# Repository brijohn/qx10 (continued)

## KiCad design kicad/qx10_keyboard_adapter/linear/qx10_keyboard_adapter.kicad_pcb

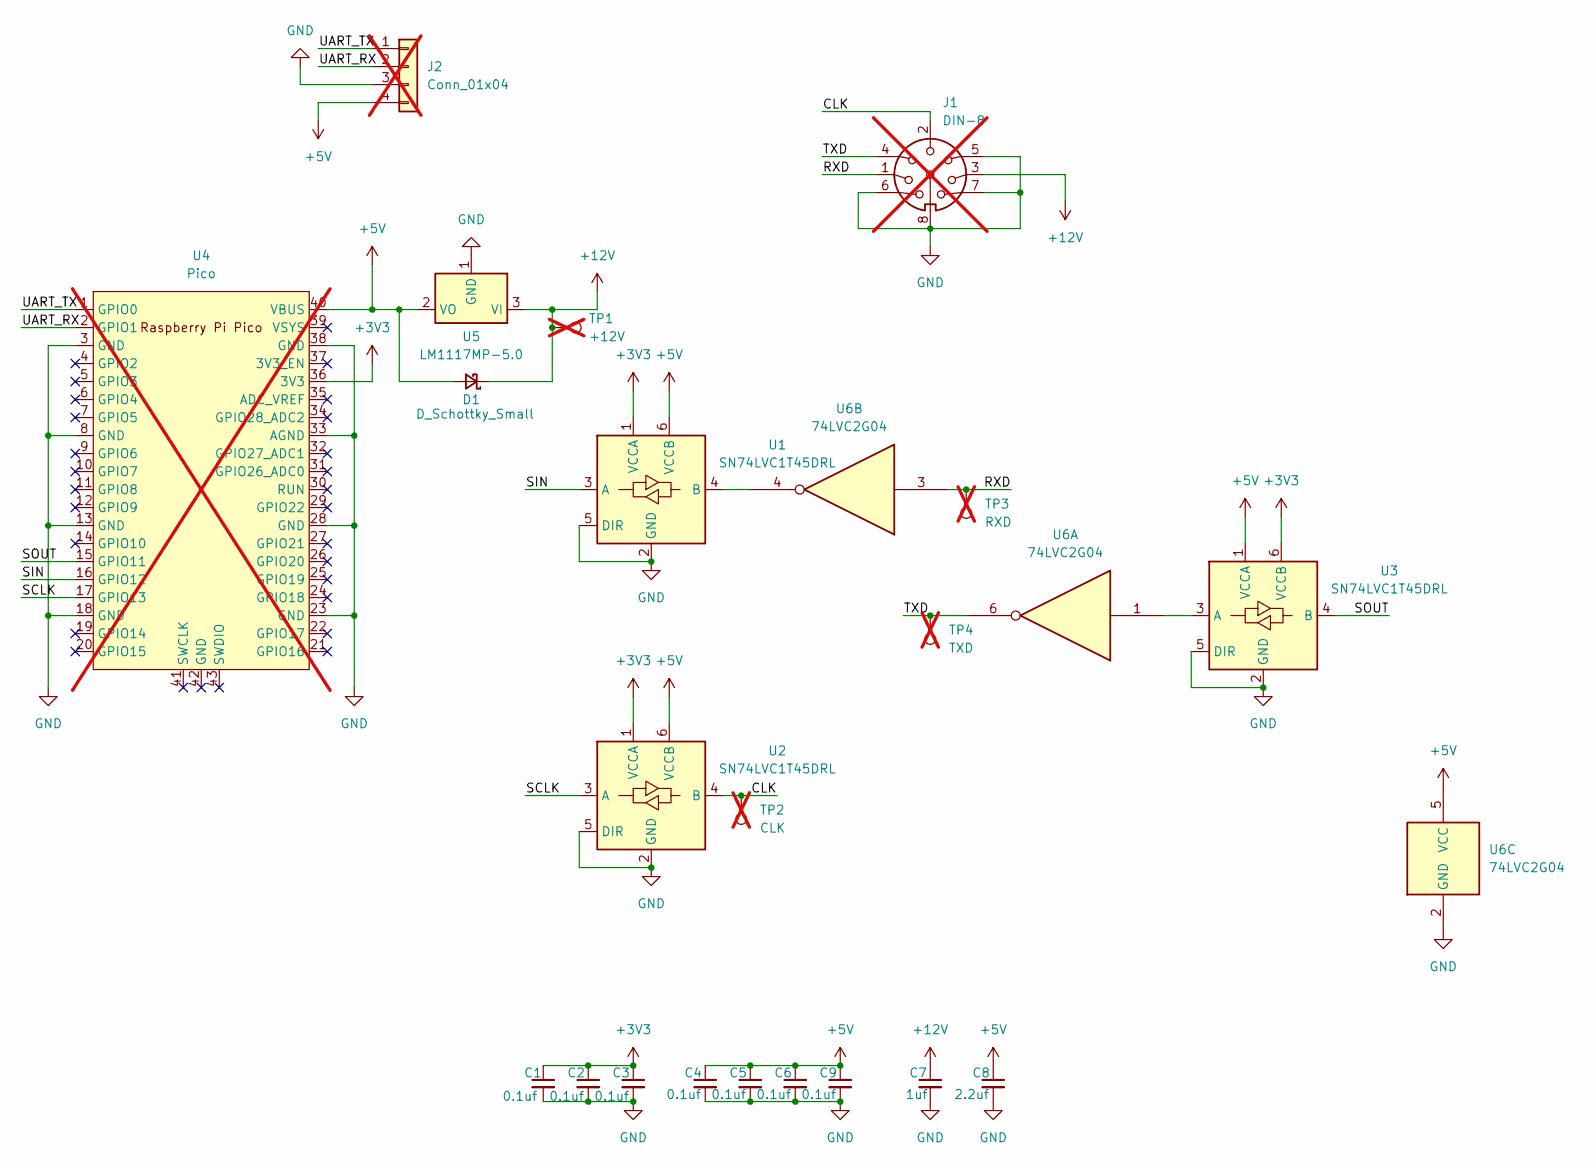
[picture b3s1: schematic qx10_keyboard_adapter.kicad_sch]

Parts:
C1, C2, C3, C4, C5, C6, C9: 0.1uf; C_0603_1608Metric_Pad1.08x0.95mm_HandSolder; JLC 0603
C7: 1uf; C_0603_1608Metric_Pad1.08x0.95mm_HandSolder; JLC 0603
C8: 2.2uf; C_0603_1608Metric_Pad1.08x0.95mm_HandSolder; JLC 0603
D1: D_Schottky_Small; D_SMA_Handsoldering; JLC SMA(DO-214AC)
J1: DIN-8; 8DIN262; not fitted
J2: Conn_01x04; PinHeader_1x04_P2.54mm_Vertical; not fitted
TP1: +12V; TestPoint_Pad_2.5x2.5mm; not fitted
TP2: CLK; TestPoint_Pad_2.5x2.5mm; not fitted
TP3: RXD; TestPoint_Pad_2.5x2.5mm; not fitted
TP4: TXD; TestPoint_Pad_2.5x2.5mm; not fitted
U1, U2, U3: SN74LVC1T45DRL; SOT-563; JLC SOT-5x3-6
U4: Pico; RPi_Pico_SMD_TH; not fitted
U5: LM1117MP-5.0; SOT-223-3_TabPin2; JLC SOT-223
U6: 74LVC2G04; SOT-23-6; JLC SOT-23-6

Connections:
+3V3: C1.1, C2.1, C3.1, U1.1 (VCCA), U2.1 (VCCA), U3.6 (VCCB), U4.36 (3V3)
+5V: C4.1, C5.1, C6.1, C8.1, C9.1, D1.2 (A), J2.4, U1.6 (VCCB), U2.6 (VCCB), U3.1 (VCCA), U4.40 (VBUS), U5.2 (VO), U6.5 (VCC)
+12V: C7.1, D1.1 (K), J1.3, TP1.1, U5.3 (VI)
/CLK: J1.2, TP2.1, U2.4 (B)
/RXD: J1.1, TP3.1, U6.3
/SCLK: U2.3 (A), U4.17 (GPIO13)
/SIN: U1.3 (A), U4.16 (GPIO12)
/SOUT: U3.4 (B), U4.15 (GPIO11)
/TXD: J1.4, TP4.1, U6.6
/UART_RX: J2.2, U4.2 (GPIO1)
/UART_TX: J2.1, U4.1 (GPIO0)
GND: C1.2, C2.2, C3.2, C4.2, C5.2, C6.2, C7.2, C8.2, C9.2, J1.5, J1.6, J1.7, J1.8, J2.3, U1.2 (GND), U1.5 (DIR), U2.2 (GND), U2.5 (DIR), U3.2 (GND), U3.5 (DIR), U4.3 (GND), U4.8 (GND), U4.13 (GND), U4.18 (GND), U4.23 (GND), U4.28 (GND), U4.33 (AGND), U4.38 (GND), U5.1 (GND), U6.2 (GND)
unnamed: U1.4 (B), U6.4
unnamed: U3.3 (A), U6.1

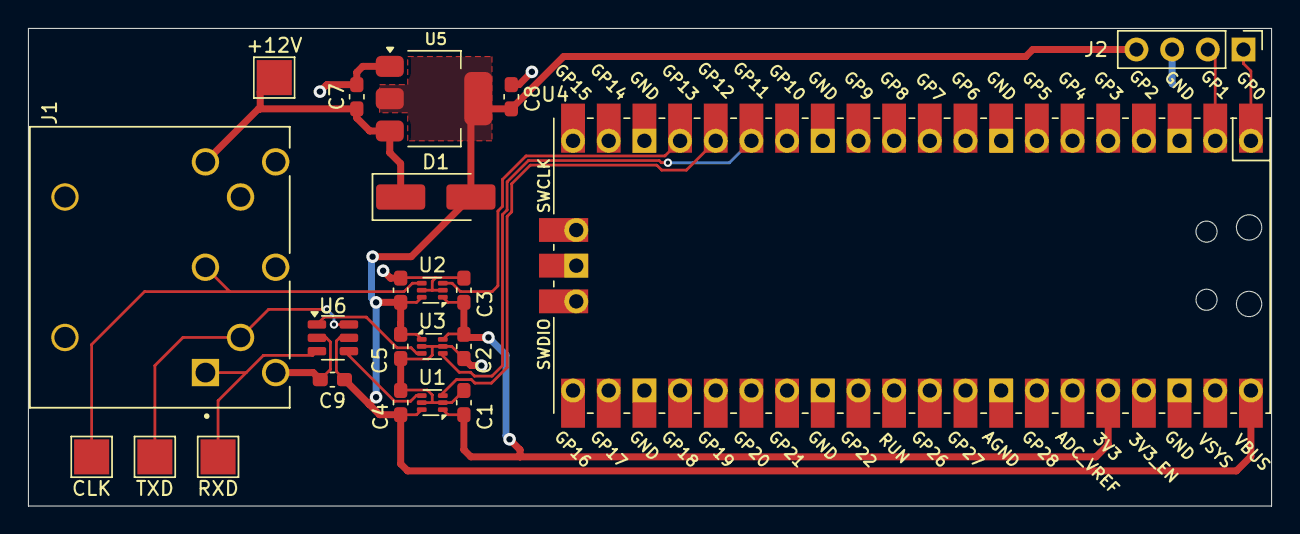
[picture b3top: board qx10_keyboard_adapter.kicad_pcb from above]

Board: 2 copper layers, 88.5 x 34.0 mm, 22 parts (0 on the bottom side), 14 nets.

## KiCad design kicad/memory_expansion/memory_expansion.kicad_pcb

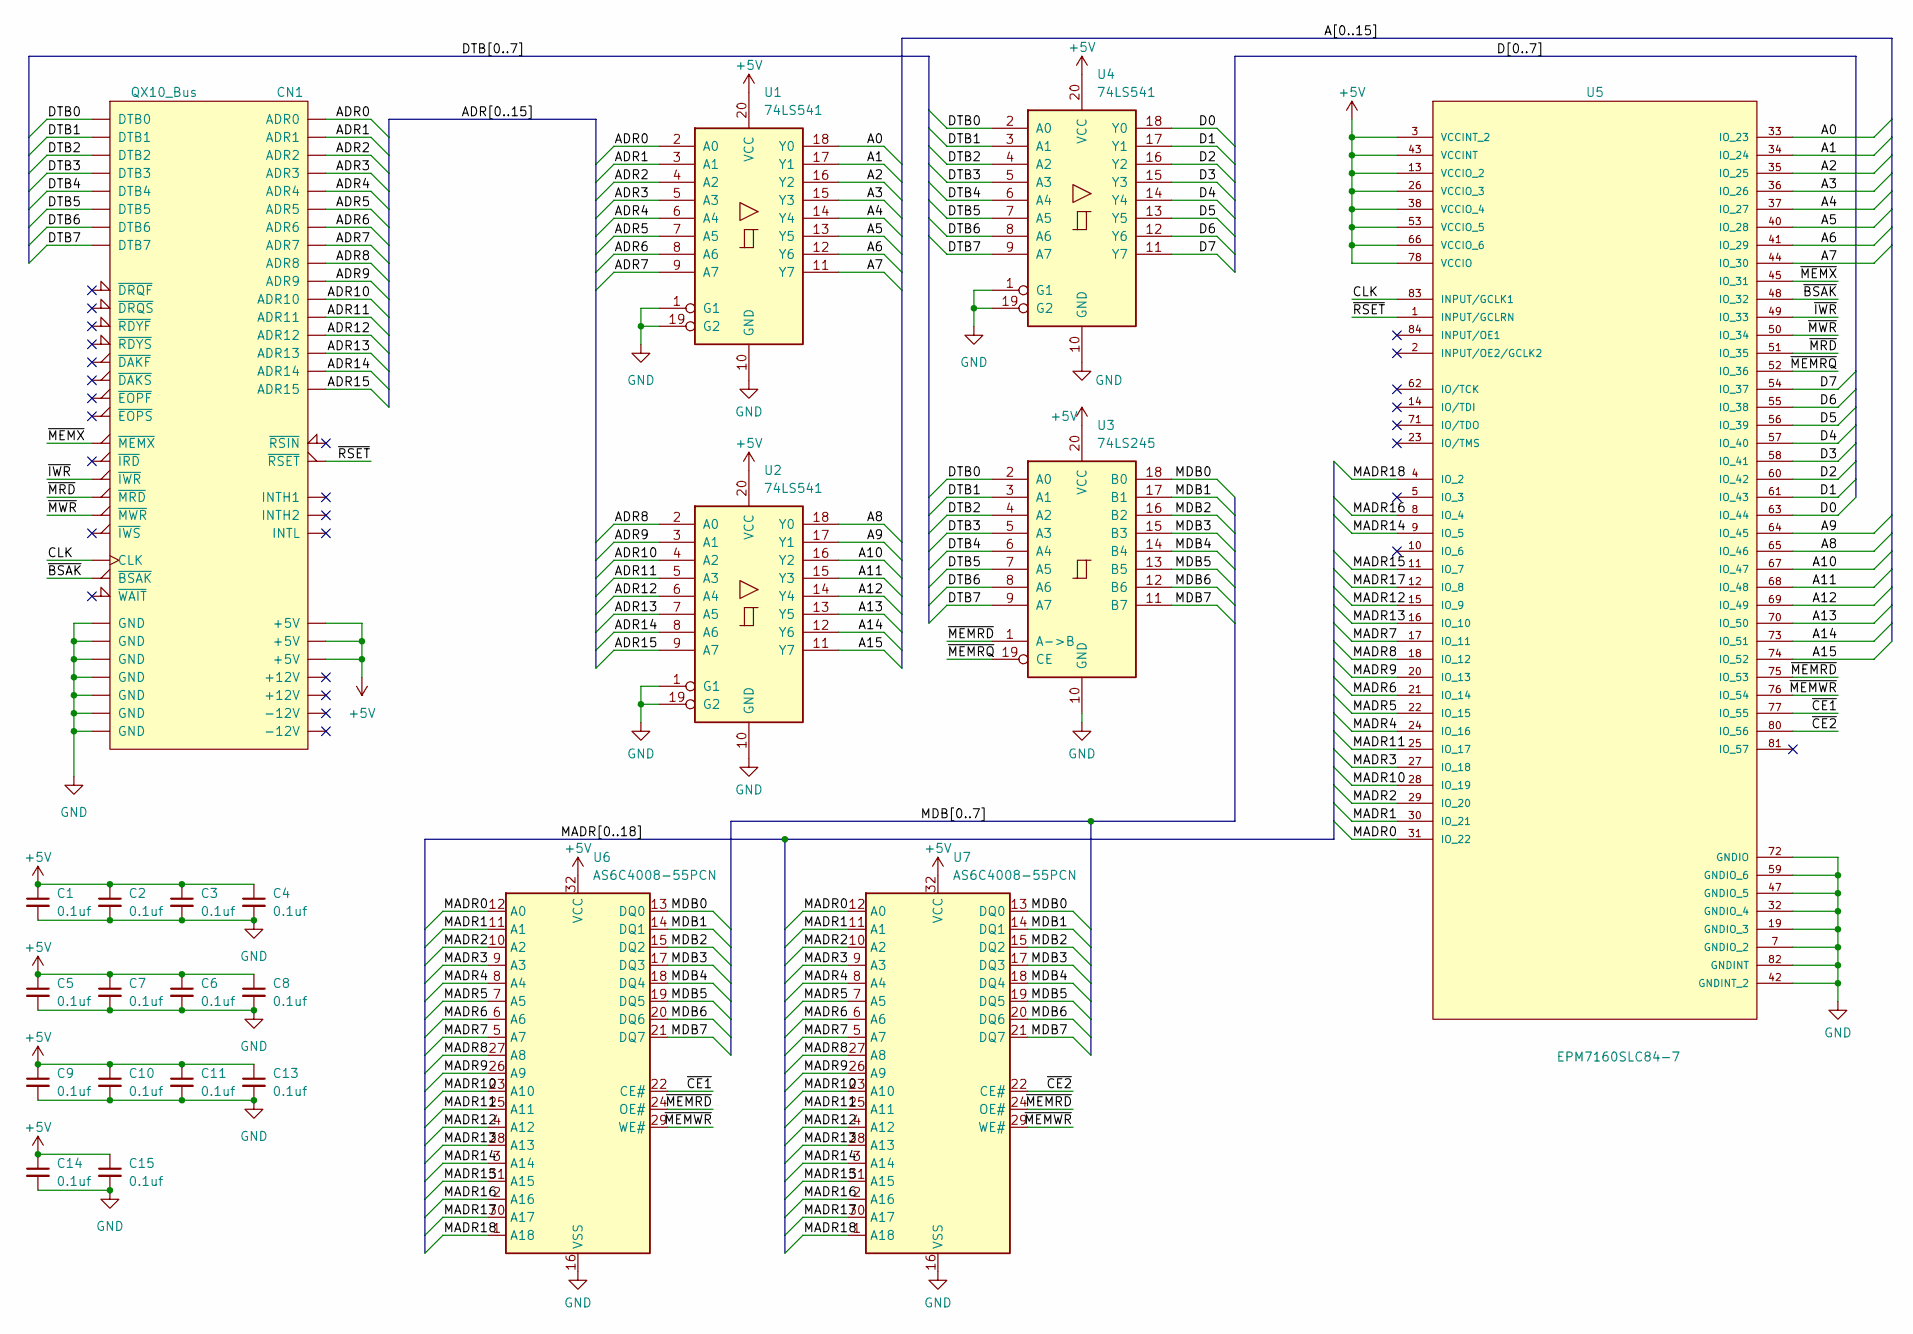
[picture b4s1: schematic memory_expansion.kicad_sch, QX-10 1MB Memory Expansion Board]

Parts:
C1, C2, C3, C4, C5, C6, C7, C8, C9, C10, C11, C13, C14, C15: 0.1uf; C_Disc_D5.0mm_W2.5mm_P2.50mm; Mouser 81-RDER72A104K1S1H3A
CN1: QX10_Bus; BUS_QX10
U1, U2, U4: 74LS541; DIP-20_W7.62mm_LongPads; Mouser 595-SN74LS541N
U3: 74LS245; DIP-20_W7.62mm_LongPads; Mouser 595-SN74LS245N
U5: EPM7160SLC84-7; PLCC-84_THT-Socket; Digikey 2057-PLCC-84-AT-ND
U6, U7: AS6C4008-55PCN; DIP-32_W15.24mm_Socket_LongPads; Mouser 913-AS6C4008-55PCN

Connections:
+5V: C1.1, C2.1, C3.1, C4.1, C5.1, C6.1, C7.1, C8.1, C9.1, C10.1, C11.1, C13.1, C14.1, C15.1, CN1.43 (+5V), CN1.45 (+5V), CN1.46 (+5V), U1.20 (VCC), U2.20 (VCC), U3.20 (VCC), U4.20 (VCC), U5.3 (VCCINT_2), U5.13 (VCCIO_2), U5.26 (VCCIO_3), U5.38 (VCCIO_4), U5.43 (VCCINT), U5.53 (VCCIO_5), U5.66 (VCCIO_6), U5.78 (VCCIO), U6.32 (VCC), U7.32 (VCC)
/A0: U1.18 (Y0), U5.33 (IO_23)
/A1: U1.17 (Y1), U5.34 (IO_24)
/A2: U1.16 (Y2), U5.35 (IO_25)
/A3: U1.15 (Y3), U5.36 (IO_26)
/A4: U1.14 (Y4), U5.37 (IO_27)
/A5: U1.13 (Y5), U5.40 (IO_28)
/A6: U1.12 (Y6), U5.41 (IO_29)
/A7: U1.11 (Y7), U5.44 (IO_30)
/A8: U2.18 (Y0), U5.65 (IO_46)
/A9: U2.17 (Y1), U5.64 (IO_45)
/A10: U2.16 (Y2), U5.67 (IO_47)
/A11: U2.15 (Y3), U5.68 (IO_48)
/A12: U2.14 (Y4), U5.69 (IO_49)
/A13: U2.13 (Y5), U5.70 (IO_50)
/A14: U2.12 (Y6), U5.73 (IO_51)
/A15: U2.11 (Y7), U5.74 (IO_52)
/ADR0: CN1.13 (ADR0), U1.2 (A0)
/ADR1: CN1.14 (ADR1), U1.3 (A1)
/ADR2: CN1.15 (ADR2), U1.4 (A2)
/ADR3: CN1.16 (ADR3), U1.5 (A3)
/ADR4: CN1.17 (ADR4), U1.6 (A4)
/ADR5: CN1.18 (ADR5), U1.7 (A5)
/ADR6: CN1.19 (ADR6), U1.8 (A6)
/ADR7: CN1.20 (ADR7), U1.9 (A7)
/ADR8: CN1.21 (ADR8), U2.2 (A0)
/ADR9: CN1.22 (ADR9), U2.3 (A1)
/ADR10: CN1.23 (ADR10), U2.4 (A2)
/ADR11: CN1.24 (ADR11), U2.5 (A3)
/ADR12: CN1.25 (ADR12), U2.6 (A4)
/ADR13: CN1.26 (ADR13), U2.7 (A5)
/ADR14: CN1.27 (ADR14), U2.8 (A6)
/ADR15: CN1.28 (ADR15), U2.9 (A7)
/CLK: CN1.31 (CLK), U5.83 (INPUT/GCLK1)
/D0: U4.18 (Y0), U5.63 (IO_44)
/D1: U4.17 (Y1), U5.61 (IO_43)
/D2: U4.16 (Y2), U5.60 (IO_42)
/D3: U4.15 (Y3), U5.58 (IO_41)
/D4: U4.14 (Y4), U5.57 (IO_40)
/D5: U4.13 (Y5), U5.56 (IO_39)
/D6: U4.12 (Y6), U5.55 (IO_38)
/D7: U4.11 (Y7), U5.54 (IO_37)
/DTB0: CN1.3 (DTB0), U3.2 (A0), U4.2 (A0)
/DTB1: CN1.4 (DTB1), U3.3 (A1), U4.3 (A1)
/DTB2: CN1.5 (DTB2), U3.4 (A2), U4.4 (A2)
/DTB3: CN1.6 (DTB3), U3.5 (A3), U4.5 (A3)
/DTB4: CN1.7 (DTB4), U3.6 (A4), U4.6 (A4)
/DTB5: CN1.8 (DTB5), U3.7 (A5), U4.7 (A5)
/DTB6: CN1.9 (DTB6), U3.8 (A6), U4.8 (A6)
/DTB7: CN1.10 (DTB7), U3.9 (A7), U4.9 (A7)
/MADR0: U5.31 (IO_22), U6.12 (A0), U7.12 (A0)
/MADR1: U5.30 (IO_21), U6.11 (A1), U7.11 (A1)
/MADR2: U5.29 (IO_20), U6.10 (A2), U7.10 (A2)
/MADR3: U5.27 (IO_18), U6.9 (A3), U7.9 (A3)
/MADR4: U5.24 (IO_16), U6.8 (A4), U7.8 (A4)
/MADR5: U5.22 (IO_15), U6.7 (A5), U7.7 (A5)
/MADR6: U5.21 (IO_14), U6.6 (A6), U7.6 (A6)
/MADR7: U5.17 (IO_11), U6.5 (A7), U7.5 (A7)
/MADR8: U5.18 (IO_12), U6.27 (A8), U7.27 (A8)
/MADR9: U5.20 (IO_13), U6.26 (A9), U7.26 (A9)
/MADR10: U5.28 (IO_19), U6.23 (A10), U7.23 (A10)
/MADR11: U5.25 (IO_17), U6.25 (A11), U7.25 (A11)
/MADR12: U5.15 (IO_9), U6.4 (A12), U7.4 (A12)
/MADR13: U5.16 (IO_10), U6.28 (A13), U7.28 (A13)
/MADR14: U5.9 (IO_5), U6.3 (A14), U7.3 (A14)
/MADR15: U5.11 (IO_7), U6.31 (A15), U7.31 (A15)
/MADR16: U5.8 (IO_4), U6.2 (A16), U7.2 (A16)
/MADR17: U5.12 (IO_8), U6.30 (A17), U7.30 (A17)
/MADR18: U5.4 (IO_2), U6.1 (A18), U7.1 (A18)
/MDB0: U3.18 (B0), U6.13 (DQ0), U7.13 (DQ0)
/MDB1: U3.17 (B1), U6.14 (DQ1), U7.14 (DQ1)
/MDB2: U3.16 (B2), U6.15 (DQ2), U7.15 (DQ2)
/MDB3: U3.15 (B3), U6.17 (DQ3), U7.17 (DQ3)
/MDB4: U3.14 (B4), U6.18 (DQ4), U7.18 (DQ4)
/MDB5: U3.13 (B5), U6.19 (DQ5), U7.19 (DQ5)
/MDB6: U3.12 (B6), U6.20 (DQ6), U7.20 (DQ6)
/MDB7: U3.11 (B7), U6.21 (DQ7), U7.21 (DQ7)
/~BSAK: CN1.33 (~BSAK), U5.48 (IO_32)
/~CE1: U5.77 (IO_55), U6.22 (CE#)
/~CE2: U5.80 (IO_56), U7.22 (CE#)
/~IWR: CN1.36 (~IWR), U5.49 (IO_33)
/~MEMRD: U3.1 (A->B), U5.75 (IO_53), U6.24 (OE#), U7.24 (OE#)
/~MEMRQ: U3.19 (CE), U5.52 (IO_36)
/~MEMWR: U5.76 (IO_54), U6.29 (WE#), U7.29 (WE#)
/~MEMX: CN1.34 (~MEMX), U5.45 (IO_31)
/~MRD: CN1.37 (~MRD), U5.51 (IO_35)
/~MWR: CN1.38 (~MWR), U5.50 (IO_34)
/~RSET: CN1.44 (~RSET), U5.1 (INPUT/GCLRN)
GND: C1.2, C2.2, C3.2, C4.2, C5.2, C6.2, C7.2, C8.2, C9.2, C10.2, C11.2, C13.2, C14.2, C15.2, CN1.1 (GND), CN1.2 (GND), CN1.29 (GND), CN1.30 (GND), CN1.32 (GND), CN1.59 (GND), CN1.60 (GND), U1.1 (G1), U1.10 (GND), U1.19 (G2), U2.1 (G1), U2.10 (GND), U2.19 (G2), U3.10 (GND), U4.1 (G1), U4.10 (GND), U4.19 (G2), U5.7 (GNDIO_2), U5.19 (GNDIO_3), U5.32 (GNDIO_4), U5.42 (GNDINT_2), U5.47 (GNDIO_5), U5.59 (GNDIO_6), U5.72 (GNDIO), U5.82 (GNDINT), U6.16 (VSS), U7.16 (VSS)

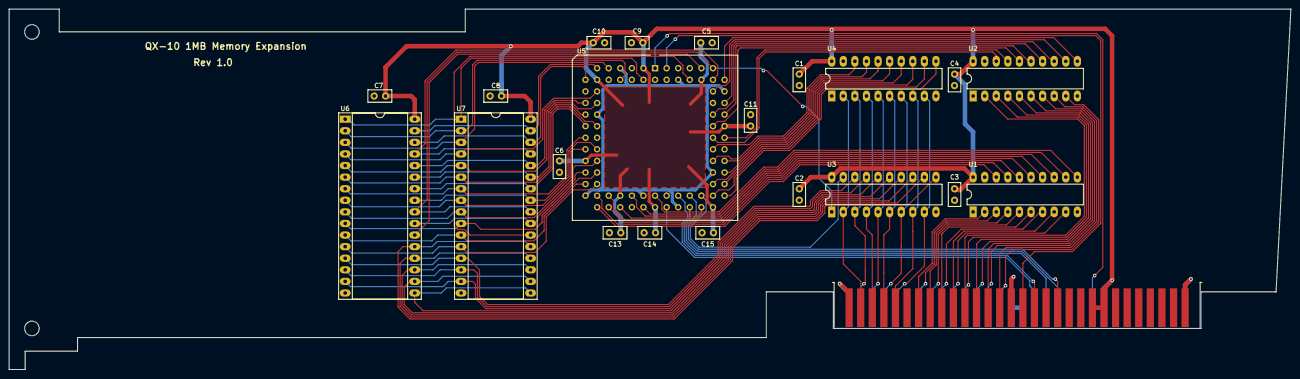
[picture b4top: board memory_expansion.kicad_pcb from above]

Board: 2 copper layers, 281.0 x 79.0 mm, 22 parts (0 on the bottom side), 89 nets.

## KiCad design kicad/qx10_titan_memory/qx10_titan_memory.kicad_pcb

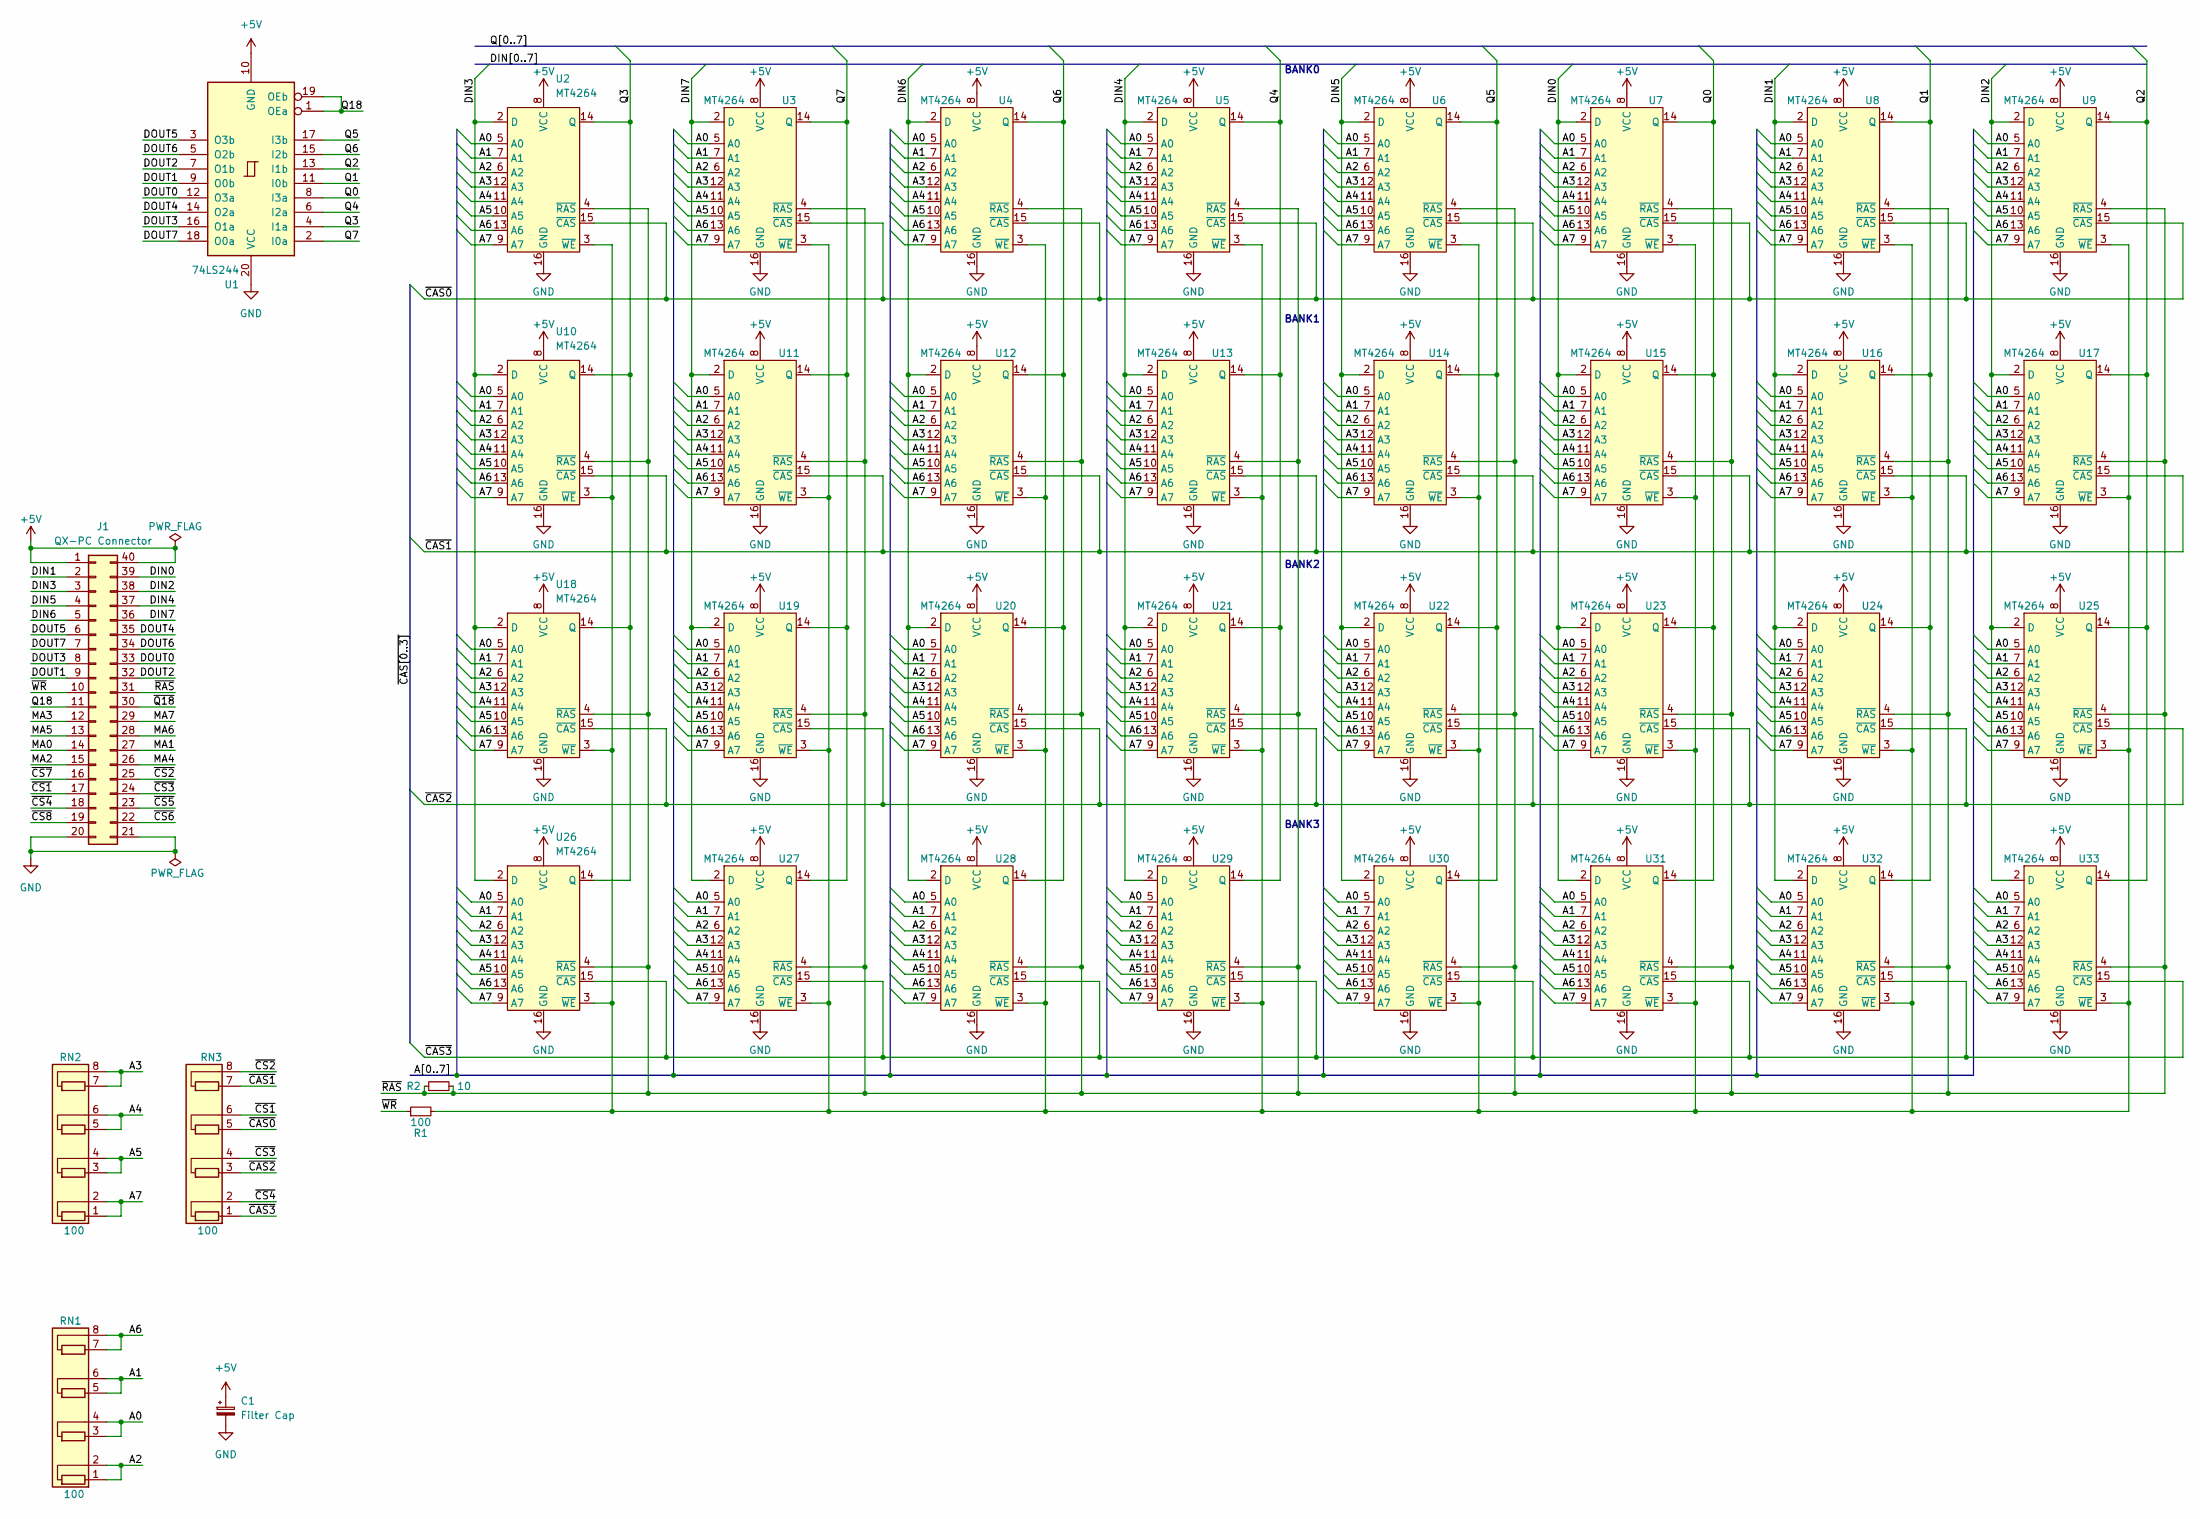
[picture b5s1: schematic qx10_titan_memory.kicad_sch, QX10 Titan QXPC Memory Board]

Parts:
C1: Filter Cap; CP_Radial_D5.0mm_P2.50mm
J1: QX-PC Connector; PinHeader_2x20_P2.54mm_Vertical
R1: 100; R_Axial_DIN0207_L6.3mm_D2.5mm_P10.16mm_Horizontal
R2: 10; R_Axial_DIN0207_L6.3mm_D2.5mm_P10.16mm_Horizontal
RN1, RN2, RN3: 100; R_Array_SIP8
U1: 74LS244; DIP-20_W7.62mm_Socket
U2, U3, U4, U5, U6, U7, U8, U9, U10, U11, U12, U13, U14, U15, U16, U17, U18, U19, U20, U21, U22, U23, U24, U25, U26, U27, U28, U29, U30, U31, U32, U33: MT4264; DIP-16_W7.62mm_Socket

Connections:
+5V: C1.1, J1.1, J1.40, U1.10 (GND), U2.8 (VCC), U3.8 (VCC), U4.8 (VCC), U5.8 (VCC), U6.8 (VCC), U7.8 (VCC), U8.8 (VCC), U9.8 (VCC), U10.8 (VCC), U11.8 (VCC), U12.8 (VCC), U13.8 (VCC), U14.8 (VCC), U15.8 (VCC), U16.8 (VCC), U17.8 (VCC), U18.8 (VCC), U19.8 (VCC), U20.8 (VCC), U21.8 (VCC), U22.8 (VCC), U23.8 (VCC), U24.8 (VCC), U25.8 (VCC), U26.8 (VCC), U27.8 (VCC), U28.8 (VCC), U29.8 (VCC), U30.8 (VCC), U31.8 (VCC), U32.8 (VCC), U33.8 (VCC)
/A0: RN1.3 (R2.1), RN1.4 (R2.2), U2.5 (A0), U3.5 (A0), U4.5 (A0), U5.5 (A0), U6.5 (A0), U7.5 (A0), U8.5 (A0), U9.5 (A0), U10.5 (A0), U11.5 (A0), U12.5 (A0), U13.5 (A0), U14.5 (A0), U15.5 (A0), U16.5 (A0), U17.5 (A0), U18.5 (A0), U19.5 (A0), U20.5 (A0), U21.5 (A0), U22.5 (A0), U23.5 (A0), U24.5 (A0), U25.5 (A0), U26.5 (A0), U27.5 (A0), U28.5 (A0), U29.5 (A0), U30.5 (A0), U31.5 (A0), U32.5 (A0), U33.5 (A0)
/A1: RN1.5 (R3.1), RN1.6 (R3.2), U2.7 (A1), U3.7 (A1), U4.7 (A1), U5.7 (A1), U6.7 (A1), U7.7 (A1), U8.7 (A1), U9.7 (A1), U10.7 (A1), U11.7 (A1), U12.7 (A1), U13.7 (A1), U14.7 (A1), U15.7 (A1), U16.7 (A1), U17.7 (A1), U18.7 (A1), U19.7 (A1), U20.7 (A1), U21.7 (A1), U22.7 (A1), U23.7 (A1), U24.7 (A1), U25.7 (A1), U26.7 (A1), U27.7 (A1), U28.7 (A1), U29.7 (A1), U30.7 (A1), U31.7 (A1), U32.7 (A1), U33.7 (A1)
/A2: RN1.1 (R1.1), RN1.2 (R1.2), U2.6 (A2), U3.6 (A2), U4.6 (A2), U5.6 (A2), U6.6 (A2), U7.6 (A2), U8.6 (A2), U9.6 (A2), U10.6 (A2), U11.6 (A2), U12.6 (A2), U13.6 (A2), U14.6 (A2), U15.6 (A2), U16.6 (A2), U17.6 (A2), U18.6 (A2), U19.6 (A2), U20.6 (A2), U21.6 (A2), U22.6 (A2), U23.6 (A2), U24.6 (A2), U25.6 (A2), U26.6 (A2), U27.6 (A2), U28.6 (A2), U29.6 (A2), U30.6 (A2), U31.6 (A2), U32.6 (A2), U33.6 (A2)
/A3: RN2.7 (R4.1), RN2.8 (R4.2), U2.12 (A3), U3.12 (A3), U4.12 (A3), U5.12 (A3), U6.12 (A3), U7.12 (A3), U8.12 (A3), U9.12 (A3), U10.12 (A3), U11.12 (A3), U12.12 (A3), U13.12 (A3), U14.12 (A3), U15.12 (A3), U16.12 (A3), U17.12 (A3), U18.12 (A3), U19.12 (A3), U20.12 (A3), U21.12 (A3), U22.12 (A3), U23.12 (A3), U24.12 (A3), U25.12 (A3), U26.12 (A3), U27.12 (A3), U28.12 (A3), U29.12 (A3), U30.12 (A3), U31.12 (A3), U32.12 (A3), U33.12 (A3)
/A4: RN2.5 (R3.1), RN2.6 (R3.2), U2.11 (A4), U3.11 (A4), U4.11 (A4), U5.11 (A4), U6.11 (A4), U7.11 (A4), U8.11 (A4), U9.11 (A4), U10.11 (A4), U11.11 (A4), U12.11 (A4), U13.11 (A4), U14.11 (A4), U15.11 (A4), U16.11 (A4), U17.11 (A4), U18.11 (A4), U19.11 (A4), U20.11 (A4), U21.11 (A4), U22.11 (A4), U23.11 (A4), U24.11 (A4), U25.11 (A4), U26.11 (A4), U27.11 (A4), U28.11 (A4), U29.11 (A4), U30.11 (A4), U31.11 (A4), U32.11 (A4), U33.11 (A4)
/A5: RN2.3 (R2.1), RN2.4 (R2.2), U2.10 (A5), U3.10 (A5), U4.10 (A5), U5.10 (A5), U6.10 (A5), U7.10 (A5), U8.10 (A5), U9.10 (A5), U10.10 (A5), U11.10 (A5), U12.10 (A5), U13.10 (A5), U14.10 (A5), U15.10 (A5), U16.10 (A5), U17.10 (A5), U18.10 (A5), U19.10 (A5), U20.10 (A5), U21.10 (A5), U22.10 (A5), U23.10 (A5), U24.10 (A5), U25.10 (A5), U26.10 (A5), U27.10 (A5), U28.10 (A5), U29.10 (A5), U30.10 (A5), U31.10 (A5), U32.10 (A5), U33.10 (A5)
/A6: RN1.7 (R4.1), RN1.8 (R4.2), U2.13 (A6), U3.13 (A6), U4.13 (A6), U5.13 (A6), U6.13 (A6), U7.13 (A6), U8.13 (A6), U9.13 (A6), U10.13 (A6), U11.13 (A6), U12.13 (A6), U13.13 (A6), U14.13 (A6), U15.13 (A6), U16.13 (A6), U17.13 (A6), U18.13 (A6), U19.13 (A6), U20.13 (A6), U21.13 (A6), U22.13 (A6), U23.13 (A6), U24.13 (A6), U25.13 (A6), U26.13 (A6), U27.13 (A6), U28.13 (A6), U29.13 (A6), U30.13 (A6), U31.13 (A6), U32.13 (A6), U33.13 (A6)
/A7: RN2.1 (R1.1), RN2.2 (R1.2), U2.9 (A7), U3.9 (A7), U4.9 (A7), U5.9 (A7), U6.9 (A7), U7.9 (A7), U8.9 (A7), U9.9 (A7), U10.9 (A7), U11.9 (A7), U12.9 (A7), U13.9 (A7), U14.9 (A7), U15.9 (A7), U16.9 (A7), U17.9 (A7), U18.9 (A7), U19.9 (A7), U20.9 (A7), U21.9 (A7), U22.9 (A7), U23.9 (A7), U24.9 (A7), U25.9 (A7), U26.9 (A7), U27.9 (A7), U28.9 (A7), U29.9 (A7), U30.9 (A7), U31.9 (A7), U32.9 (A7), U33.9 (A7)
/DIN0: J1.39, U7.2 (D), U15.2 (D), U23.2 (D), U31.2 (D)
/DIN1: J1.2, U8.2 (D), U16.2 (D), U24.2 (D), U32.2 (D)
/DIN2: J1.38, U9.2 (D), U17.2 (D), U25.2 (D), U33.2 (D)
/DIN3: J1.3, U2.2 (D), U10.2 (D), U18.2 (D), U26.2 (D)
/DIN4: J1.37, U5.2 (D), U13.2 (D), U21.2 (D), U29.2 (D)
/DIN5: J1.4, U6.2 (D), U14.2 (D), U22.2 (D), U30.2 (D)
/DIN6: J1.5, U4.2 (D), U12.2 (D), U20.2 (D), U28.2 (D)
/DIN7: J1.36, U3.2 (D), U11.2 (D), U19.2 (D), U27.2 (D)
/DOUT0: J1.33, U1.12 (O3a)
/DOUT1: J1.9, U1.9 (O0b)
/DOUT2: J1.32, U1.7 (O1b)
/DOUT3: J1.8, U1.16 (O1a)
/DOUT4: J1.35, U1.14 (O2a)
/DOUT5: J1.6, U1.3 (O3b)
/DOUT6: J1.34, U1.5 (O2b)
/DOUT7: J1.7, U1.18 (O0a)
/MA0: J1.14
/MA1: J1.27
/MA2: J1.15
/MA3: J1.12
/MA4: J1.26
/MA5: J1.13
/MA6: J1.28
/MA7: J1.29
/Q0: U1.8 (I3a), U7.14 (Q), U15.14 (Q), U23.14 (Q), U31.14 (Q)
/Q1: U1.11 (I0b), U8.14 (Q), U16.14 (Q), U24.14 (Q), U32.14 (Q)
/Q2: U1.13 (I1b), U9.14 (Q), U17.14 (Q), U25.14 (Q), U33.14 (Q)
/Q3: U1.4 (I1a), U2.14 (Q), U10.14 (Q), U18.14 (Q), U26.14 (Q)
/Q4: U1.6 (I2a), U5.14 (Q), U13.14 (Q), U21.14 (Q), U29.14 (Q)
/Q5: U1.17 (I3b), U6.14 (Q), U14.14 (Q), U22.14 (Q), U30.14 (Q)
/Q6: U1.15 (I2b), U4.14 (Q), U12.14 (Q), U20.14 (Q), U28.14 (Q)
/Q7: U1.2 (I0a), U3.14 (Q), U11.14 (Q), U19.14 (Q), U27.14 (Q)
/Q18: J1.11, U1.1 (OEa), U1.19 (OEb)
/~CAS0: RN3.5 (R3.1), U2.15 (~CAS), U3.15 (~CAS), U4.15 (~CAS), U5.15 (~CAS), U6.15 (~CAS), U7.15 (~CAS), U8.15 (~CAS), U9.15 (~CAS)
/~CAS1: RN3.7 (R4.1), U10.15 (~CAS), U11.15 (~CAS), U12.15 (~CAS), U13.15 (~CAS), U14.15 (~CAS), U15.15 (~CAS), U16.15 (~CAS), U17.15 (~CAS)
/~CAS2: RN3.3 (R2.1), U18.15 (~CAS), U19.15 (~CAS), U20.15 (~CAS), U21.15 (~CAS), U22.15 (~CAS), U23.15 (~CAS), U24.15 (~CAS), U25.15 (~CAS)
/~CAS3: RN3.1 (R1.1), U26.15 (~CAS), U27.15 (~CAS), U28.15 (~CAS), U29.15 (~CAS), U30.15 (~CAS), U31.15 (~CAS), U32.15 (~CAS), U33.15 (~CAS)
/~CS1: J1.17, RN3.6 (R3.2)
/~CS2: J1.25, RN3.8 (R4.2)
/~CS3: J1.24, RN3.4 (R2.2)
/~CS4: J1.18, RN3.2 (R1.2)
/~CS5: J1.23
/~CS6: J1.22
/~CS7: J1.16
/~CS8: J1.19
/~Q18: J1.30
/~RAS: J1.31, R2.1, R2.2, U2.4 (~RAS), U3.4 (~RAS), U4.4 (~RAS), U5.4 (~RAS), U6.4 (~RAS), U7.4 (~RAS), U8.4 (~RAS), U9.4 (~RAS), U10.4 (~RAS), U11.4 (~RAS), U12.4 (~RAS), U13.4 (~RAS), U14.4 (~RAS), U15.4 (~RAS), U16.4 (~RAS), U17.4 (~RAS), U18.4 (~RAS), U19.4 (~RAS), U20.4 (~RAS), U21.4 (~RAS), U22.4 (~RAS), U23.4 (~RAS), U24.4 (~RAS), U25.4 (~RAS), U26.4 (~RAS), U27.4 (~RAS), U28.4 (~RAS), U29.4 (~RAS), U30.4 (~RAS), U31.4 (~RAS), U32.4 (~RAS), U33.4 (~RAS)
/~WR: J1.10, R1.1
GND: C1.2, J1.20, J1.21, U1.20 (VCC), U2.16 (GND), U3.16 (GND), U4.16 (GND), U5.16 (GND), U6.16 (GND), U7.16 (GND), U8.16 (GND), U9.16 (GND), U10.16 (GND), U11.16 (GND), U12.16 (GND), U13.16 (GND), U14.16 (GND), U15.16 (GND), U16.16 (GND), U17.16 (GND), U18.16 (GND), U19.16 (GND), U20.16 (GND), U21.16 (GND), U22.16 (GND), U23.16 (GND), U24.16 (GND), U25.16 (GND), U26.16 (GND), U27.16 (GND), U28.16 (GND), U29.16 (GND), U30.16 (GND), U31.16 (GND), U32.16 (GND), U33.16 (GND)
unnamed: R1.2, U2.3 (~WE), U3.3 (~WE), U4.3 (~WE), U5.3 (~WE), U6.3 (~WE), U7.3 (~WE), U8.3 (~WE), U9.3 (~WE), U10.3 (~WE), U11.3 (~WE), U12.3 (~WE), U13.3 (~WE), U14.3 (~WE), U15.3 (~WE), U16.3 (~WE), U17.3 (~WE), U18.3 (~WE), U19.3 (~WE), U20.3 (~WE), U21.3 (~WE), U22.3 (~WE), U23.3 (~WE), U24.3 (~WE), U25.3 (~WE), U26.3 (~WE), U27.3 (~WE), U28.3 (~WE), U29.3 (~WE), U30.3 (~WE), U31.3 (~WE), U32.3 (~WE), U33.3 (~WE)

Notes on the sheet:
BANK0
BANK1
BANK3
BANK2

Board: 2 copper layers, 40 parts (0 on the bottom side), 46 nets, no tracks yet.

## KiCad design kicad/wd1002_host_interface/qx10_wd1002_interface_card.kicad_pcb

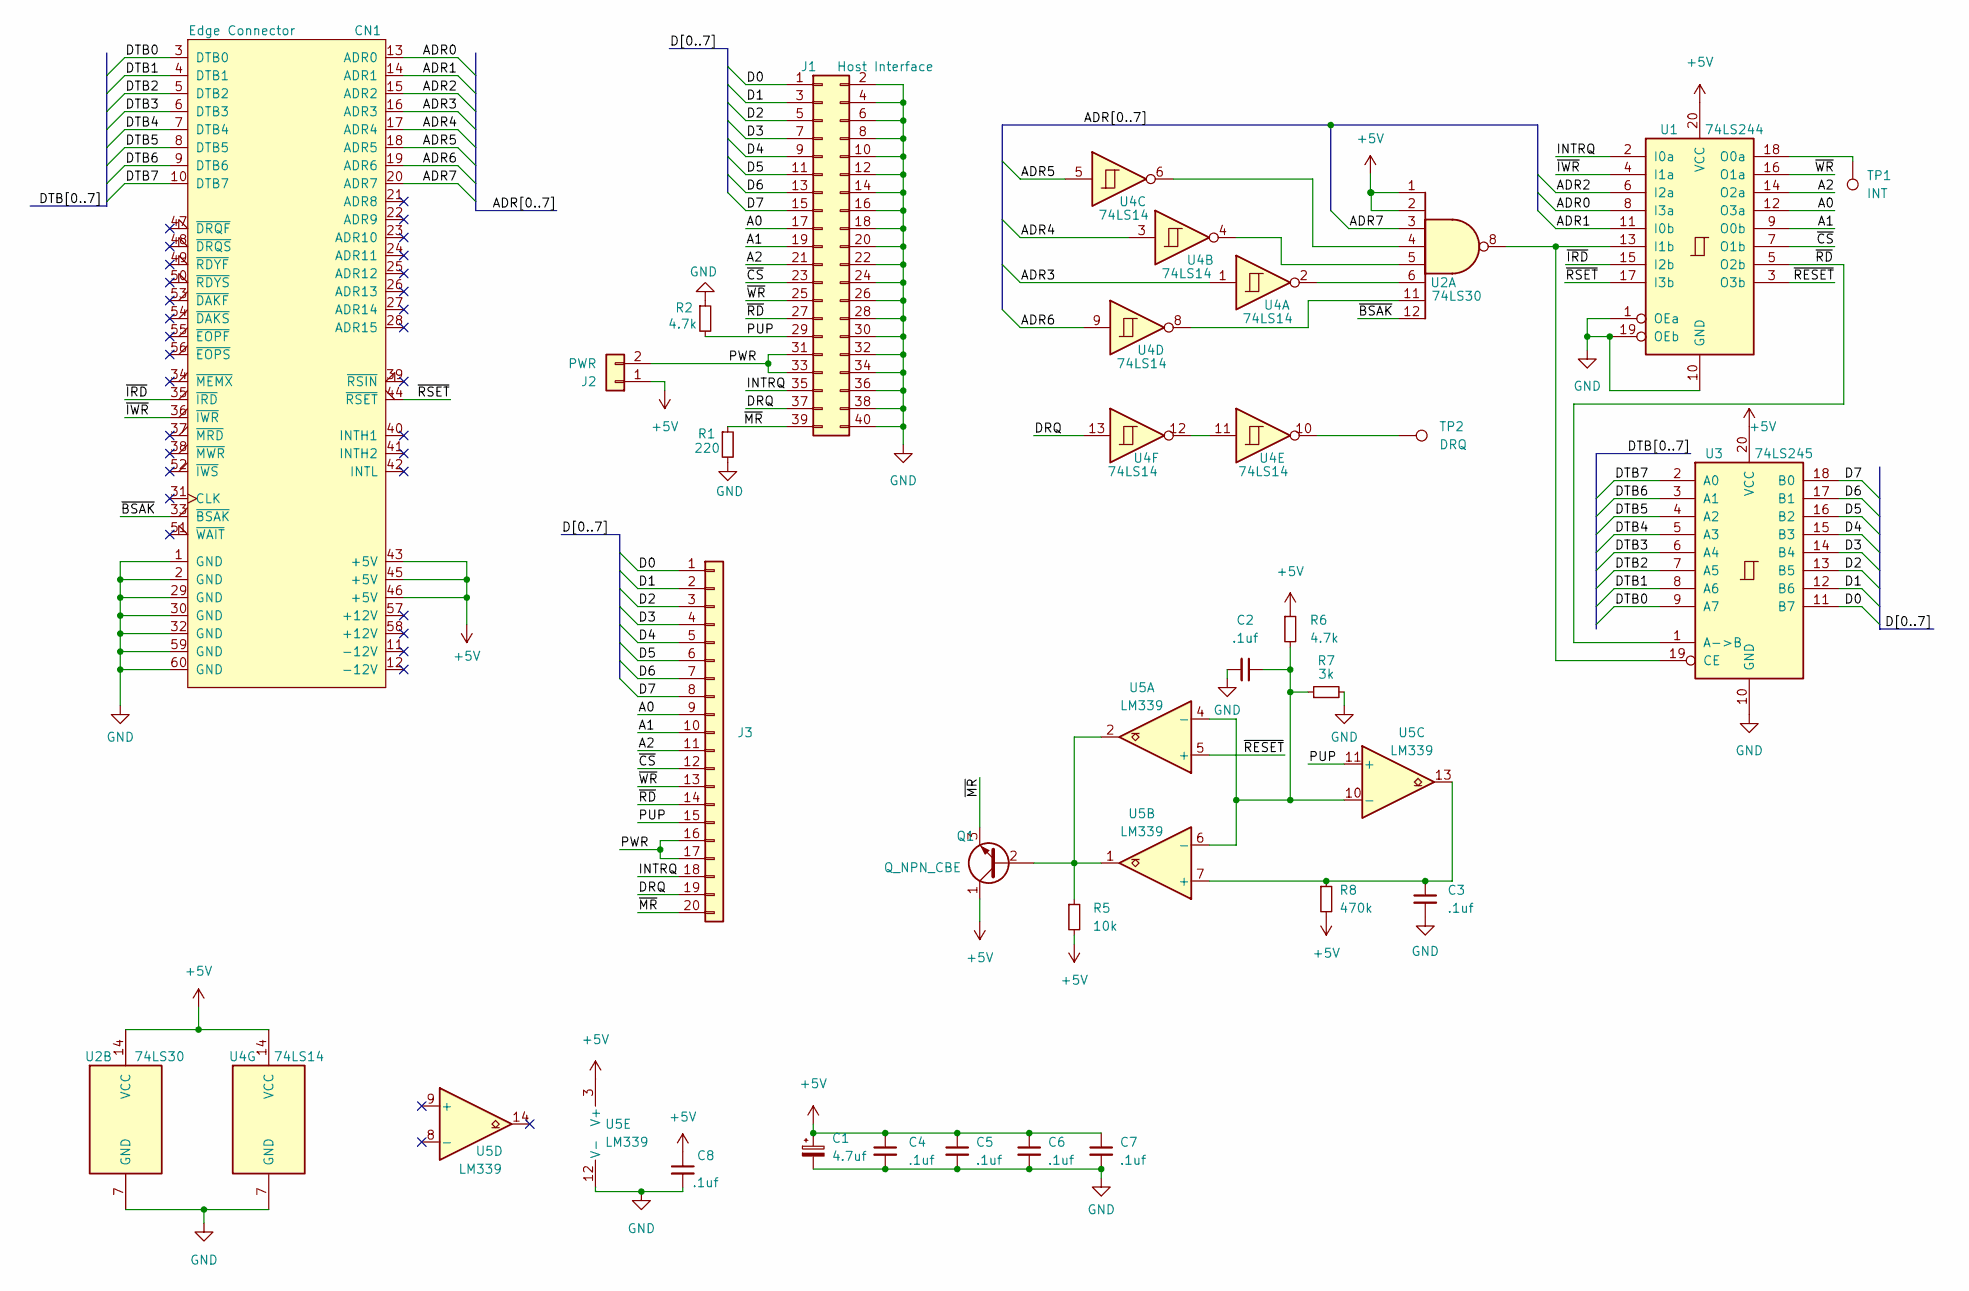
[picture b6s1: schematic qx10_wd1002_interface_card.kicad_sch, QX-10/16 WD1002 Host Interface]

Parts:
C1: 4.7uf; CP_Axial_L10.0mm_D4.5mm_P15.00mm_Horizontal; Digikey 4065PHCT-ND
C2, C3, C4, C5, C6, C7, C8: .1uf; C_Axial_L5.1mm_D3.1mm_P7.50mm_Horizontal; Digikey 399-15287-1-ND
CN1: Edge Connector; BUS_QX10
J1: Host Interface; PinHeader_2x20_P2.54mm_Horizontal
J2: PWR; PinHeader_1x02_P2.54mm_Vertical
J3: (no value)
Q1: Q_NPN_CBE; TO-92_Inline; Digikey BC33725BU-ND
R1: 220; R_Axial_DIN0207_L6.3mm_D2.5mm_P7.62mm_Horizontal; Digikey CF14JT220RCT-ND
R2, R6: 4.7k; R_Axial_DIN0207_L6.3mm_D2.5mm_P7.62mm_Horizontal; Digikey CF14JT4K70CT-ND
R5: 10k; R_Axial_DIN0207_L6.3mm_D2.5mm_P7.62mm_Horizontal; Digikey CF14JT10K0CT-ND
R7: 3k; R_Axial_DIN0207_L6.3mm_D2.5mm_P7.62mm_Horizontal; Digikey CF14JT3K00CT-ND
R8: 470k; R_Axial_DIN0207_L6.3mm_D2.5mm_P7.62mm_Horizontal; Digikey RNV14FAL470KCT-ND
TP1: INT; TestPoint_THTPad_D2.0mm_Drill1.0mm
TP2: DRQ; TestPoint_THTPad_D2.0mm_Drill1.0mm
U1: 74LS244; DIP-20_W7.62mm_LongPads; Digikey 296-1653-5-ND
U2: 74LS30; DIP-14_W7.62mm_LongPads; Digikey 296-3693-5-ND
U3: 74LS245; DIP-20_W7.62mm_LongPads; Digikey 296-1655-5-ND
U4: 74LS14; DIP-14_W7.62mm_LongPads; Digikey 296-1643-5-ND
U5: LM339; DIP-14_W7.62mm_LongPads; Digikey 296-LM339NE3-ND

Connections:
+5V: C1.1, C4.1, C5.1, C6.1, C7.1, C8.1, CN1.43 (+5V), CN1.45 (+5V), CN1.46 (+5V), J2.1, Q1.1 (C), R5.2, R6.1, R8.2, U1.20 (VCC), U2.1, U2.2, U2.14 (VCC), U3.20 (VCC), U4.14 (VCC), U5.3 (V+)
/A0: J1.17, J3.9, U1.12 (O3a)
/A1: J1.19, J3.10, U1.9 (O0b)
/A2: J1.21, J3.11, U1.14 (O2a)
/ADR0: CN1.13 (ADR0), U1.8 (I3a)
/ADR1: CN1.14 (ADR1), U1.11 (I0b)
/ADR2: CN1.15 (ADR2), U1.6 (I2a)
/ADR3: CN1.16 (ADR3), U4.1
/ADR4: CN1.17 (ADR4), U4.3
/ADR5: CN1.18 (ADR5), U4.5
/ADR6: CN1.19 (ADR6), U4.9
/ADR7: CN1.20 (ADR7), U2.3
/D0: J1.1, J3.1, U3.11 (B7)
/D1: J1.3, J3.2, U3.12 (B6)
/D2: J1.5, J3.3, U3.13 (B5)
/D3: J1.7, J3.4, U3.14 (B4)
/D4: J1.9, J3.5, U3.15 (B3)
/D5: J1.11, J3.6, U3.16 (B2)
/D6: J1.13, J3.7, U3.17 (B1)
/D7: J1.15, J3.8, U3.18 (B0)
/DRQ: J1.37, J3.19, U4.13
/DTB0: CN1.3 (DTB0), U3.9 (A7)
/DTB1: CN1.4 (DTB1), U3.8 (A6)
/DTB2: CN1.5 (DTB2), U3.7 (A5)
/DTB3: CN1.6 (DTB3), U3.6 (A4)
/DTB4: CN1.7 (DTB4), U3.5 (A3)
/DTB5: CN1.8 (DTB5), U3.4 (A2)
/DTB6: CN1.9 (DTB6), U3.3 (A1)
/DTB7: CN1.10 (DTB7), U3.2 (A0)
/INTRQ: J1.35, J3.18, U1.2 (I0a)
/PUP: J1.29, J3.15, R2.2, U5.11 (+)
/PWR: J1.31, J1.33, J2.2, J3.16, J3.17
/~BSAK: CN1.33 (~BSAK), U2.12
/~CS: J1.23, J3.12, U1.7 (O1b)
/~IRD: CN1.35 (~IRD), U1.15 (I2b)
/~IWR: CN1.36 (~IWR), U1.4 (I1a)
/~MR: J1.39, J3.20, Q1.3 (E), R1.1
/~RD: J1.27, J3.14, U1.5 (O2b), U3.1 (A->B)
/~RESET: U1.3 (O3b), U5.5 (+)
/~RSET: CN1.44 (~RSET), U1.17 (I3b)
/~WR: J1.25, J3.13, U1.16 (O1a)
GND: C1.2, C2.2, C3.2, C4.2, C5.2, C6.2, C7.2, C8.2, CN1.1 (GND), CN1.2 (GND), CN1.29 (GND), CN1.30 (GND), CN1.32 (GND), CN1.59 (GND), CN1.60 (GND), J1.2, J1.4, J1.6, J1.8, J1.10, J1.12, J1.14, J1.16, J1.18, J1.20, J1.22, J1.24, J1.26, J1.28, J1.30, J1.32, J1.34, J1.36, J1.38, J1.40, R1.2, R2.1, R7.2, U1.1 (OEa), U1.10 (GND), U1.19 (OEb), U2.7 (GND), U3.10 (GND), U4.7 (GND), U5.12 (V-)
unnamed: C2.1, R6.2, R7.1, U5.4 (-), U5.6 (-), U5.10 (-)
unnamed: C3.1, R8.1, U5.7 (+), U5.13
unnamed: Q1.2 (B), R5.1, U5.1, U5.2
unnamed: TP1.1, U1.18 (O0a)
unnamed: TP2.1, U4.10
unnamed: U1.13 (I1b), U2.8, U3.19 (CE)
unnamed: U2.4, U4.6
unnamed: U2.5, U4.4
unnamed: U2.6, U4.2
unnamed: U2.11, U4.8
unnamed: U4.11, U4.12

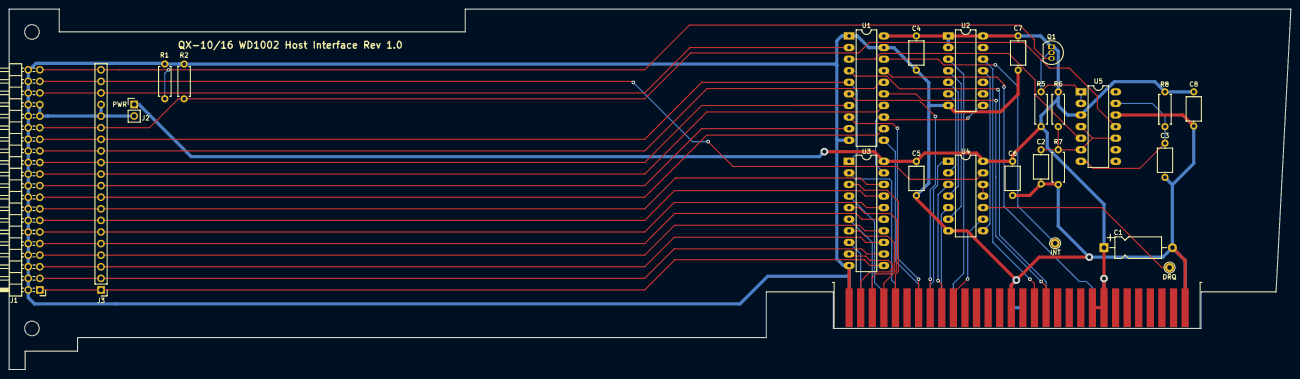
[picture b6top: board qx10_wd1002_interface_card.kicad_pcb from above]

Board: 2 copper layers, 281.0 x 79.0 mm, 26 parts (0 on the bottom side), 53 nets.
